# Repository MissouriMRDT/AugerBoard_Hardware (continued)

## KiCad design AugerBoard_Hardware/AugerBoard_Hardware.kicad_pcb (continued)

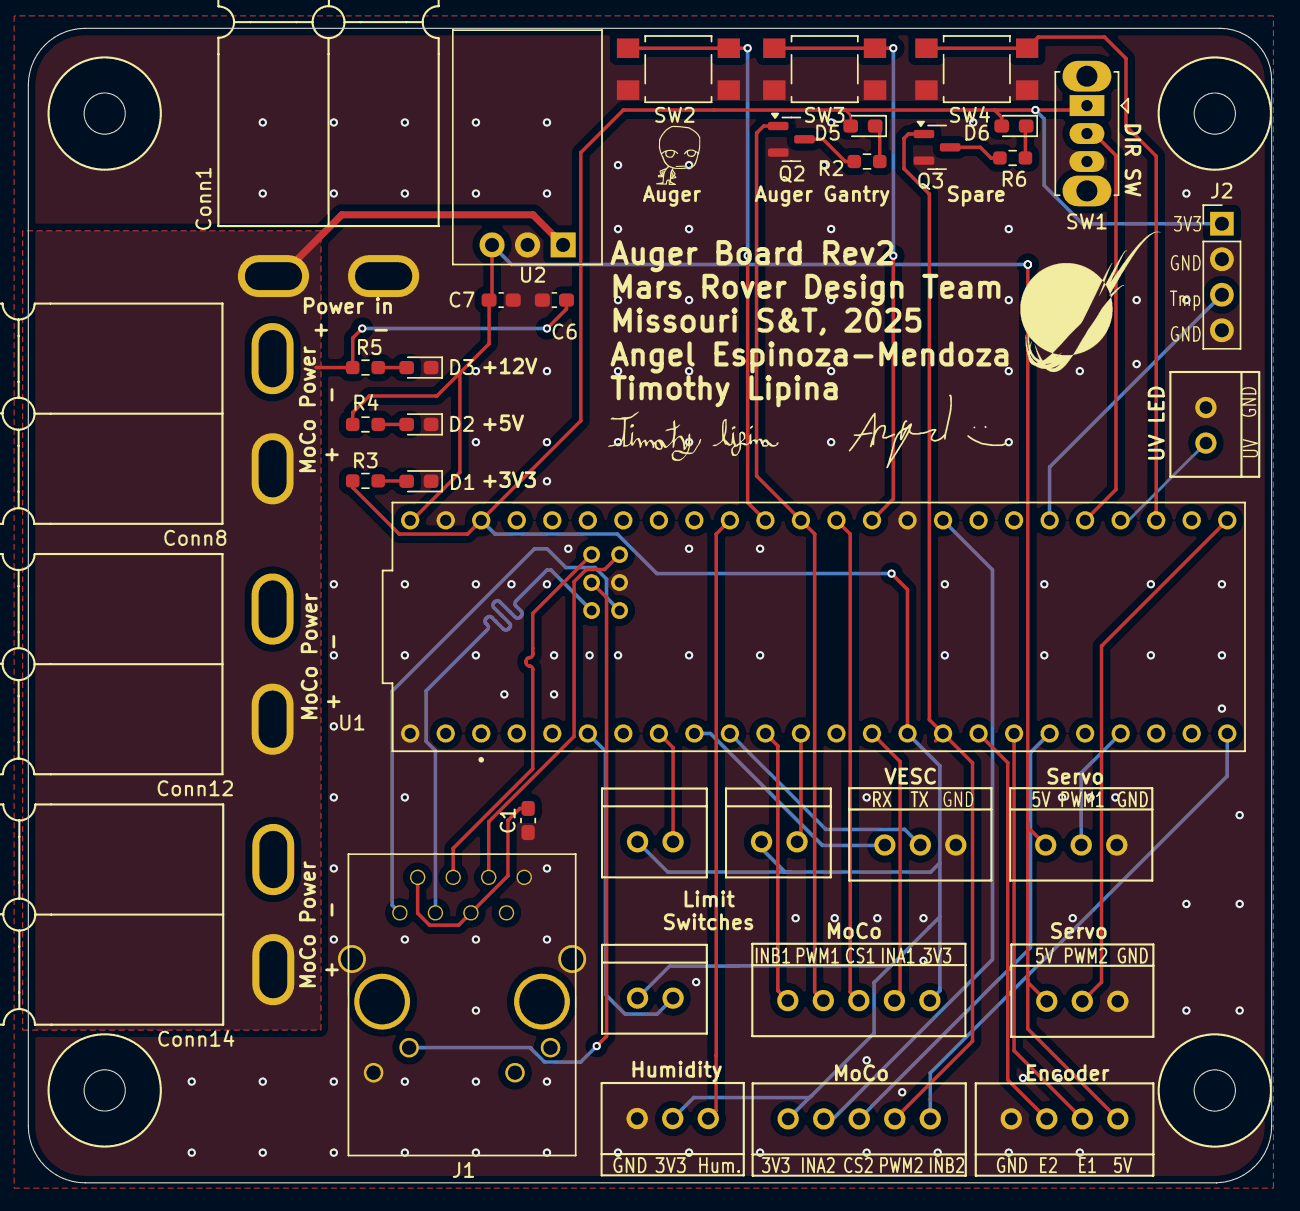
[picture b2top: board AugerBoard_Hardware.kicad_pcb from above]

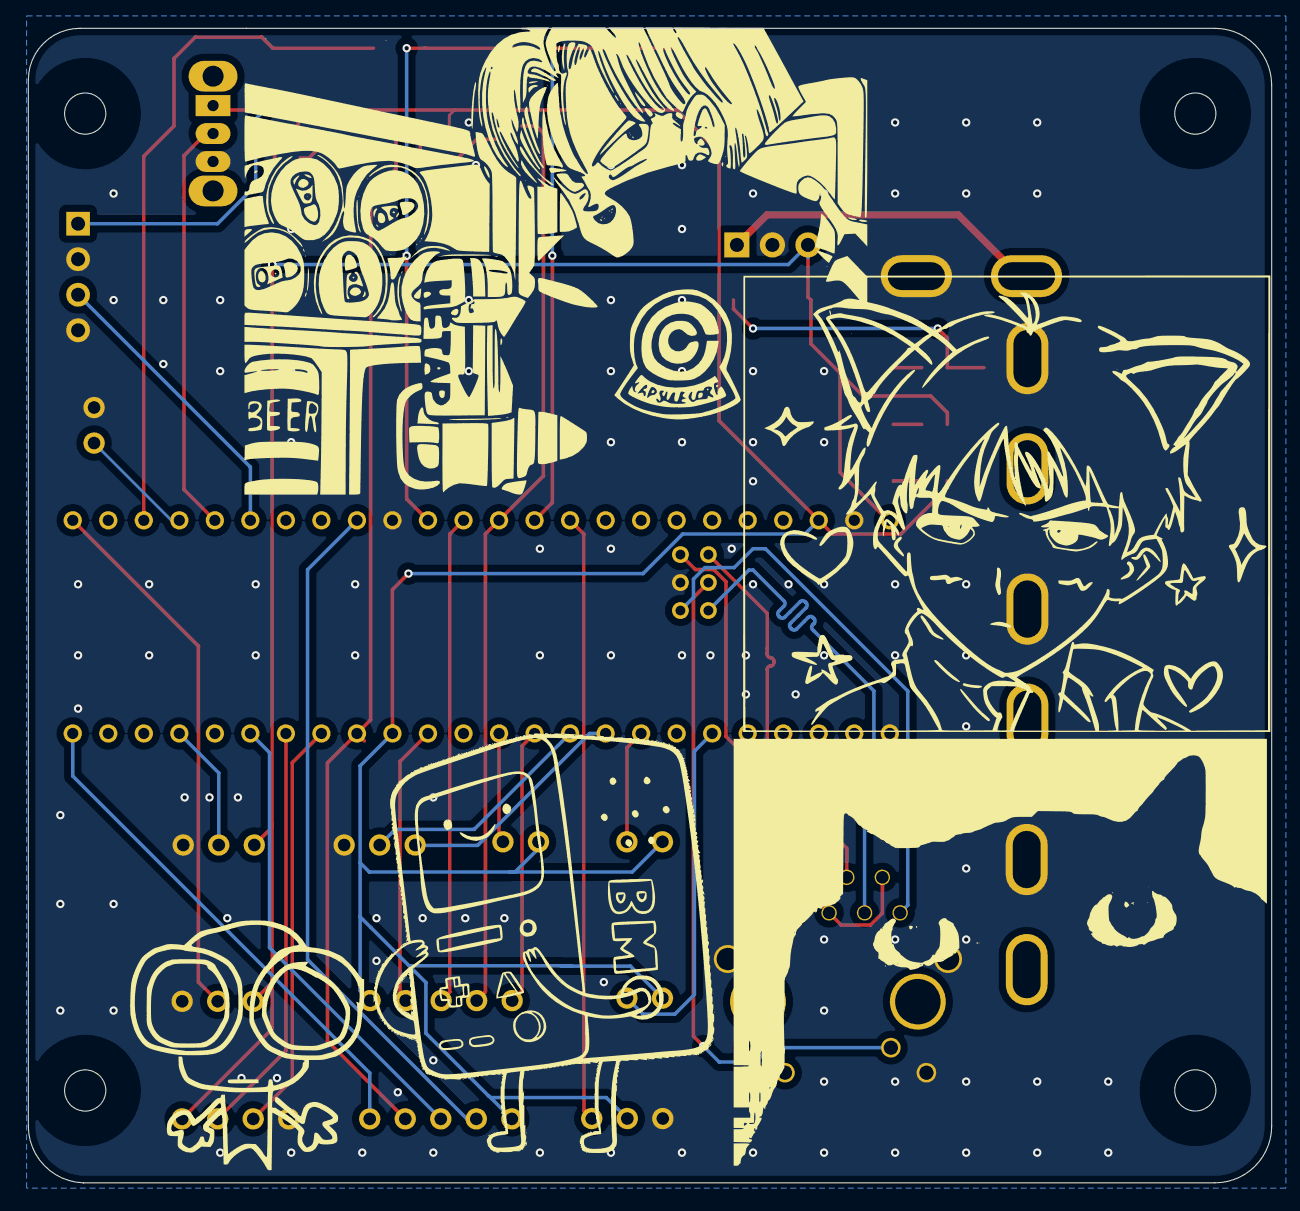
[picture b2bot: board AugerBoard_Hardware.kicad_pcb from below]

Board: 2 copper layers, 88.9 x 82.5 mm, 48 parts (4 on the bottom side), 41 nets.

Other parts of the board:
 : LOGO
‎: LOGO
‎#2, ‎#3, ‎#4: LOGO
‎‎: LOGO

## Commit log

2024-09-25 Project setup
2024-09-27 Began schematic
2024-09-27 Demonstration of push and pulling and commiting
2024-09-28 Added temp and humidity, direction switch, test buttons, and leds
2024-09-29 Added temp/humidity, switches and buttons, leds, and moco stuff
2024-10-01 Organized and Added Stuff
    Added two more test buttons. Previously we only had 2 and we have two motors so I assume that we need 2 for each motor forward and backward running.
    Will looked at our test buttons and told me they won't work but they are the same as last years so I built the version he said would work. I'm confused though because last year had the same test butt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
2024-10-01 Update to my previous comit
    Will and I realized the buttons were fine because of teensy internal pullup
2024-10-02 Added 2 more dumb moco connections
    -Still need to fix dumb moco pinouts
    -double check all pinouts
2024-10-03 Fixed and double checked all pin connections to the teensy
2024-10-04 Fixed a capacitor value
2024-10-05 Fixed LED resistor value
2024-10-10 some schematic review changes
2024-10-16 Added PWM LED
2024-10-22 Updated sensor circuits and updated BOM
2024-10-24 Footprint hai
2024-10-24 200 resistors changed to 220 for standardization
2024-10-29 Footprint changed and layout started
2024-10-29 Layout fun time yippie #based #awesome
2024-10-29 Layout made smaller hai
2024-10-30 Good first pass hai
2024-10-30 Layout made smaller h
2024-10-31 i dont know what is happening
2024-10-31 Layout finished?
2024-11-02 Fixed various clearances and silkscreen issues. Many still persist
2024-11-02 Clearance errors fixed
2024-11-02 Added some labels
2024-11-05 funny ahhh bad labels
2024-11-07 Added IR sensor/emitter and rerouted shtuff
2024-11-07 Dimensions FIXED
2024-11-07 erm the same but again hai
2024-11-09 Flipped moco connector and traces, and added labels
2024-11-09 Flipped other moco gg
2024-11-13 Some layout review changes made
2024-11-15 Layout Review Changes Made
2024-11-15 FINAL Layout Changes probably
2024-11-15 Final Rev1 Layout
2025-03-04 5 volt to teensy fixed (single worst trace ever made)
2025-03-04 UV Led connection added
2025-03-12 vesc connections added, some traces rerouted, silkscreens added
2025-03-13 just one more drawing i swear
2025-03-13 slight adjustment
2025-03-13 Schematic probably correct, layout fucked
2025-03-13 Layout and retracing
2025-03-14 Small schematic and layout fixes
2025-03-15 Silkscreen labels added
2025-03-17 ir shtuff removed, board dimensions good i think,
2025-03-17 DRC fixed and no connects added
2025-09-12 Added workflow
2025-09-30 Test commit
2025-10-01 Main Components
    started working on main components
2025-10-03 Rearranged Schematic locations
2025-10-05 Added Servo, cleaned up schematic
2025-10-05 Moved things to make more sense
2025-10-05 Added Parts, Renamed Parts
    Added in switches, buttons, & multiple anderson connections for power.
2025-10-08 added NPK and soil sensors pt. 1
2025-10-08 Soil sensors pt. 2
2025-10-08 Added Labels, Missing Requirements, and Refined Look
2025-10-09 Adjusted resistor values & renamed AF outputs
2025-10-20 Added Extra 5V out from teensy
2025-10-21 assigned footprints
2025-10-21 Started Layout
    attached Andersons and switches to a potential place
2025-10-21 Fixed issues after schematic review
    added 6 leds for every servo, changed txd and rxd to pins 30/31, added additional oki for 3.3V
2025-10-22 Edited names and locations for readability
2025-10-22 switched soil sensor ports and layout work
    soil sensor ports in fact needed to be the way they were originally after looking into the sensors we are using. Also started moving different components on layout to their spots.
2025-10-22 Layout Progress
    Made a basic setup for locations, placed preliminary wires and text, rearranged teensy pins for simplicity
2025-10-22 A little refining to the layout
    moved wires for clearance
2025-10-22 Fixed several errors in the design
    Changed font sizes, trace spacing, and added vias for grounding
2025-10-23 made minor design changes to layout
    changed 12V plane dimensions, rerouted a few traces for clearance
2025-10-23 changed trace lengths
    made minor changes to trace lengths of CAN lines
2025-10-24 Added second CAN tranceiver and a switch
    also imported a new symbol for both the switch symbol and its footprint
2025-10-24 Added Second CAN and Switch
    Retraced CAN signal lines and added a second transceiver going to a switch
2025-10-24 Equalized traces, text resizing
2025-10-24 Text location changes & more vias
2025-11-02 Dimensions, Datasheets, Gerbs files
2025-11-04 Removed Gerbs used for price
2025-11-05 Redid layout to shrink & add new power connectors
2025-11-05 Added labels for power and fixed diff pair lengths
2025-11-06 fine tuning
2025-11-06 made changes from layout review
2025-11-12 added pin for AF, added gimbal names, refined look
2025-11-12 Swapped Pins for AF
2025-11-12 3D models
2025-11-14 dimension text for mechanicals
2025-11-17 Add reverse voltage protection circuit
2025-11-17 Remove large blend files
2025-11-18 Repin AF Board Connector
2025-11-18 Caught mislabeled pinout for AF after the recent pin change
2025-12-10 Update 3D models
2026-02-18 Redesigning Layout
2026-02-18 Temporary Designed Layout for review
2026-02-18 Temporary 2nd Auger Board
2026-02-26 minor trace routing started
2026-02-26 updated teensy pinout
2026-02-27 trace progress
2026-02-27 preliminary routing
2026-02-27 Pre-board check layout
2026-02-27 finishing touch
2026-03-03 updated via sizes
2026-03-03 minor touch ups
2026-03-11 Redid 3D models
2026-03-15 added changes from board review
2026-03-16 updated based on overlord jesse's input
2026-03-16 testing pointer update
2026-03-16 retesting pointers
2026-03-16 did I fix the pointers?
2026-03-16 definitely for sure this time layout fixed
2026-03-23 Final hardware as ordered
2026-04-20 add updated step file
